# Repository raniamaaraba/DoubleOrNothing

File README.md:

# PCB Development in KiCAD
For this semester, we will be creating custom PCBs (printed circuit boards) in a free software called [KiCAD](https://www.kicad.org/download/), primarily for the use of condensing space inside the avionics bay and to move the club further towards the goal of a space shot in which custom PCBs would be critical to the development of avionics. Before we decide on a final design, in order to easily share and access the schematics, we will be using GitHub as a form of version control. Notably, before we get into the actual logistics of GitHub itself, I wanted to create a comprehensive list _(as of 2/5/26)_ of the parts that we will be using

| Coloquial Name  | Name |
| ------------- | ------------- |
| Microcontroller  | ESP32-S3  |
| Battery | LiPO  |
| Barometer | MS561101BA03-50 |
| IMU | LSM6DSO32TR |
| MOSFET| TBD |
| Resistor| Generic for now |
| Capacitor | Also Generic |

There should be a ZIP file included to help for some of the imports, if you cannot find a specific item you are looking for, please reach out to Loring. Also note the current PCBs on the main branch of KiCAD are primarily for demonstration and by no means are the current version of what we are making. 

# Forking and GitHub
Since I am the owner of this repository, I cannot demonstrate how to fork a repository but I can link you to the GitHub Page about this--click [here](https://docs.github.com/en/pull-requests/collaborating-with-pull-requests/working-with-forks/fork-a-repo) to read how before adding your own commits. This ensure that everyone can keep version control of their PCB without effecting the current main PCB. If you have any issues with Forking this repository (make sure it is the KiCAD branch), please reach out! Also want to note unlike when it come to coding development, it is significantly easier to manage uploading files and pushes using the online GitHub website rather than the desktop.

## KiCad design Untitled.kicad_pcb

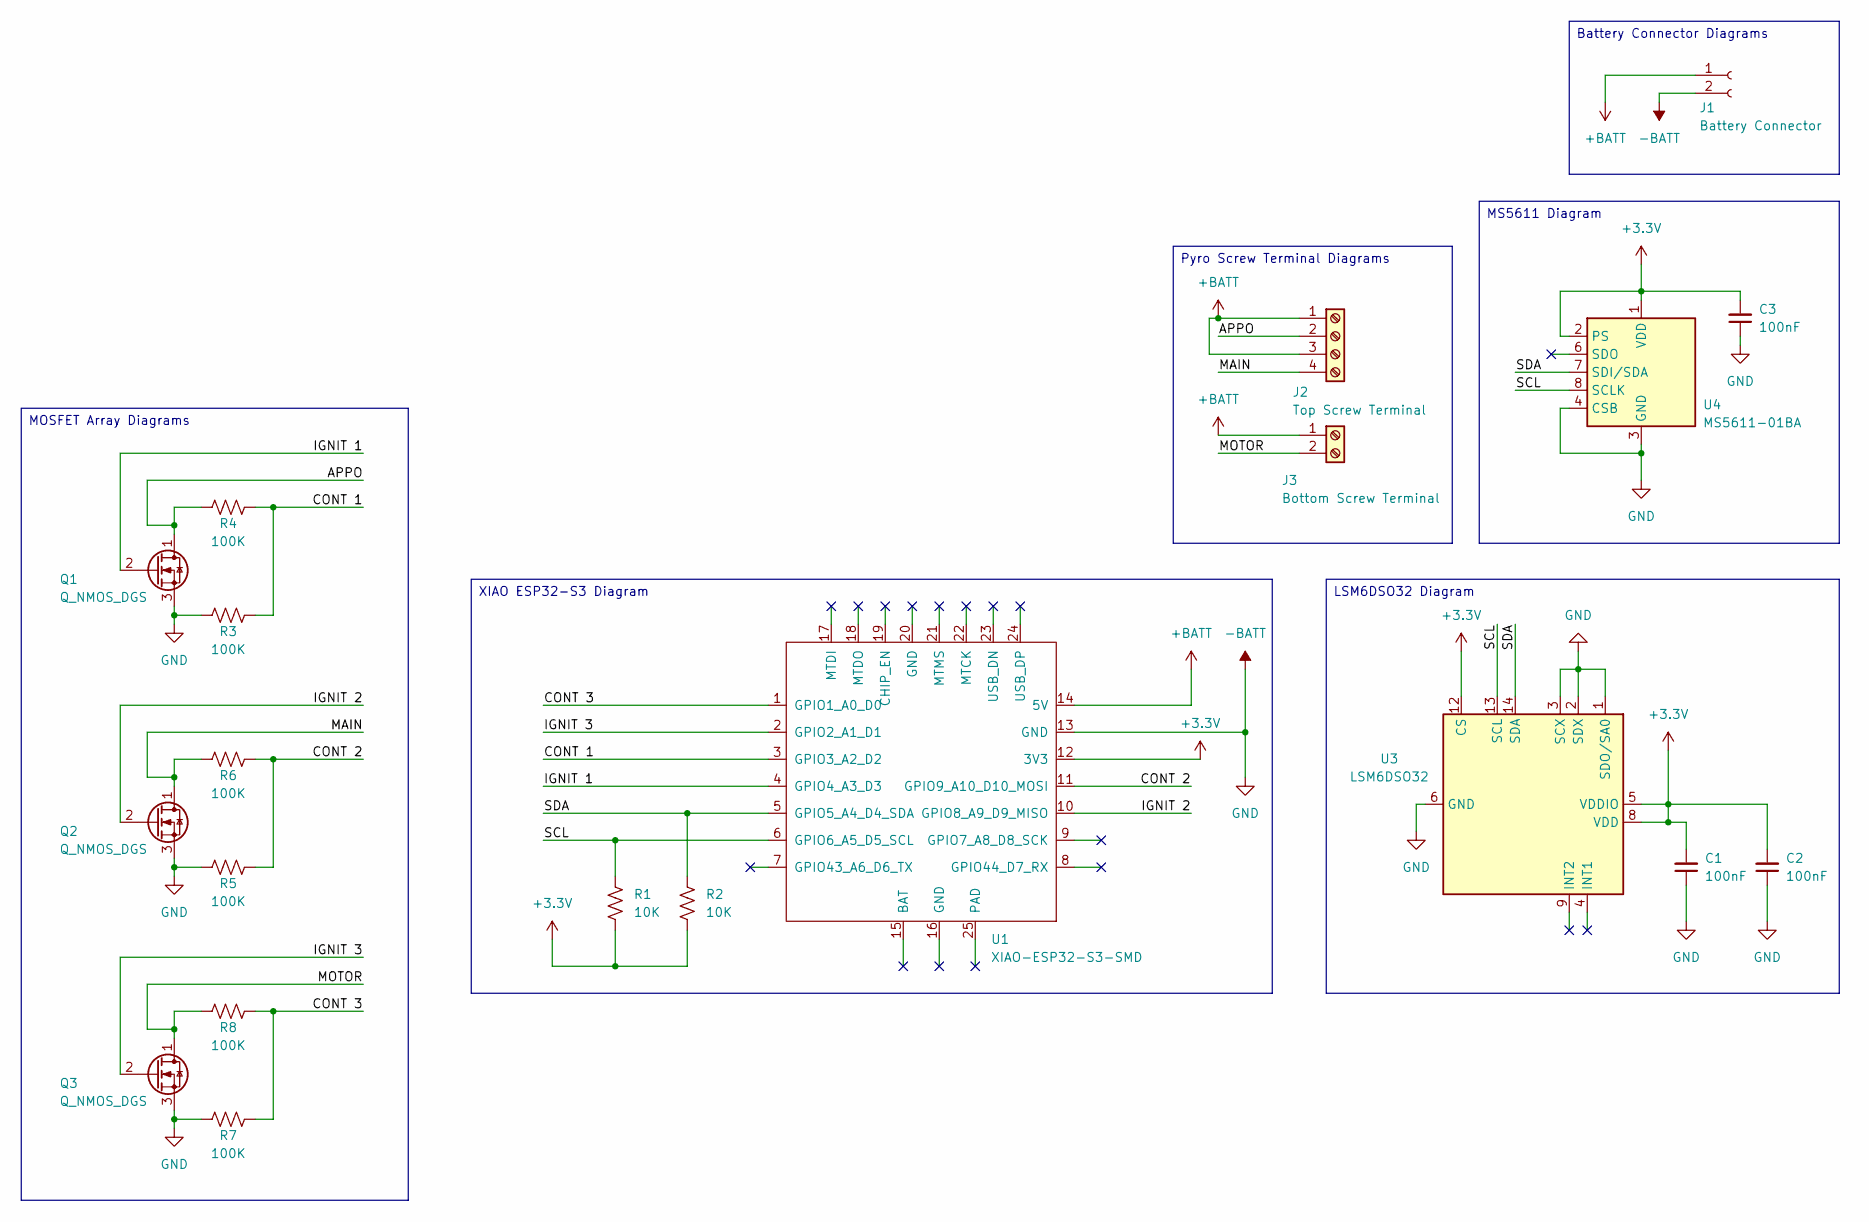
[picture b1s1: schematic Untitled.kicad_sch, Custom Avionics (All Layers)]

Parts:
C1, C2, C3: 100nF; C_0603_1608Metric
J1: Battery Connector; JST_PH_B2B-PH-K_1x02_P2.00mm_Vertical
J2: Top Screw Terminal; TerminalBlock_Phoenix_MPT-0,5-4-2.54_1x04_P2.54mm_Horizontal
J3: Bottom Screw Terminal; TerminalBlock_Phoenix_MPT-0,5-2-2.54_1x02_P2.54mm_Horizontal
Q1, Q2, Q3: Q_NMOS_DGS; TSOT-23
R1, R2: 10K; R_0402_1005Metric
R3, R4, R5, R6, R7, R8: 100K; R_0402_1005Metric
U1: XIAO-ESP32-S3-SMD; XIAO-ESP32S3-DIP
U3: LSM6DSO32; LGA-14_3x2.5mm_P0.5mm_LayoutBorder3x4y
U4: MS5611-01BA; LGA-8_3x5mm_P1.25mm

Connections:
+3.3V: C1.2, C2.2, C3.2, R1.2, R2.2, U1.12 (3V3), U3.5 (VDDIO), U3.8 (VDD), U3.12 (CS), U4.1 (VDD), U4.2 (PS)
+BATT: J1.1, J2.1, J2.3, J3.1, U1.14 (5V)
-BATT: C1.1, C2.1, C3.1, J1.2, Q1.3 (S), Q2.3 (S), Q3.3 (S), R3.2, R5.2, R7.2, U1.13 (GND), U3.1 (SDO/SA0), U3.2 (SDX), U3.3 (SCX), U3.6 (GND), U3.7 (GND), U4.3 (GND), U4.4 (CSB), U4.5 (CSB); also elsewhere on the board
/APPO: J2.2, Q1.1 (D), R4.2
/CONT 1: R3.1, R4.1, U1.3 (GPIO3_A2_D2)
/CONT 2: R5.1, R6.1, U1.11 (GPIO9_A10_D10_MOSI)
/CONT 3: R7.1, R8.1, U1.1 (GPIO1_A0_D0)
/IGNIT 1: Q1.2 (G), U1.4 (GPIO4_A3_D3); also elsewhere on the board
/IGNIT 2: Q2.2 (G), U1.10 (GPIO8_A9_D9_MISO); also elsewhere on the board
/IGNIT 3: Q3.2 (G), U1.2 (GPIO2_A1_D1); also elsewhere on the board
/MAIN: J2.4, Q2.1 (D), R6.2
/MOTOR: J3.2, Q3.1 (D), R8.2
/SCL: R1.1, U1.6 (GPIO6_A5_D5_SCL), U3.13 (SCL), U4.8 (SCLK)
/SDA: R2.1, U1.5 (GPIO5_A4_D4_SDA), U3.14 (SDA), U4.7 (SDI/SDA)

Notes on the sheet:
XIAO ESP32-S3 Diagram
LSM6DSO32 Diagram
MS5611 Diagram
Battery Connector Diagrams
MOSFET Array Diagrams
Pyro Screw Terminal Diagrams

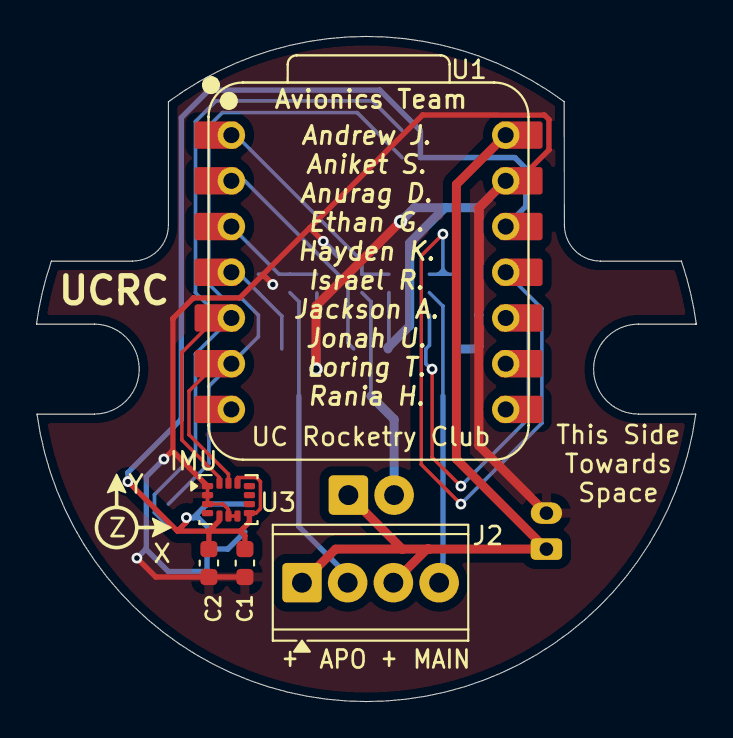
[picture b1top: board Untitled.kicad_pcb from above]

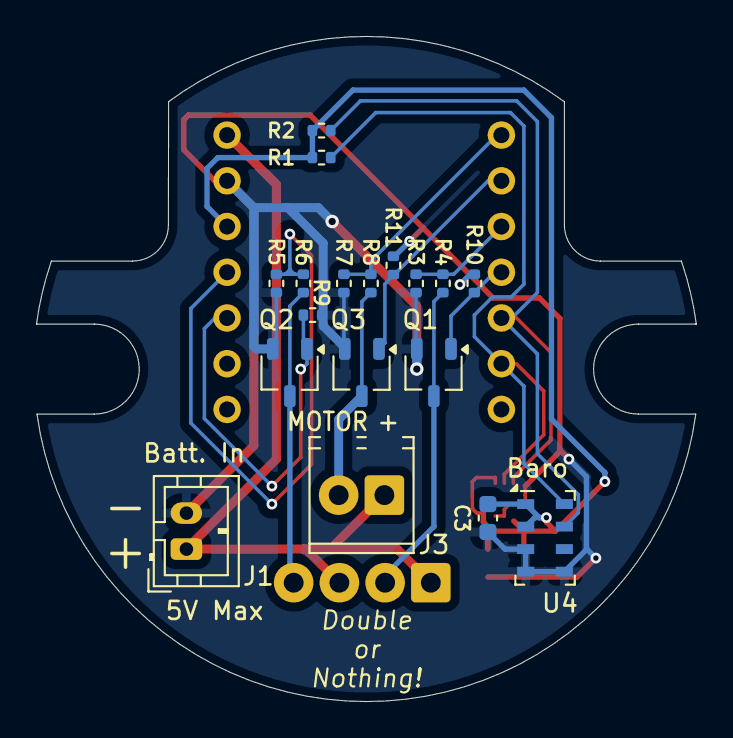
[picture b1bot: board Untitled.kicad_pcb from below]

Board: 2 copper layers, 36.7 x 37.0 mm, 23 parts (18 on the bottom side), 14 nets.

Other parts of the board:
R9, R10, R11: 4.7; R_0402_1005Metric

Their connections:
-BATT: R9.2, R10.2, R11.2; also elsewhere on the board
/IGNIT 1: R10.1; also elsewhere on the board
/IGNIT 2: R9.1; also elsewhere on the board
/IGNIT 3: R11.1; also elsewhere on the board

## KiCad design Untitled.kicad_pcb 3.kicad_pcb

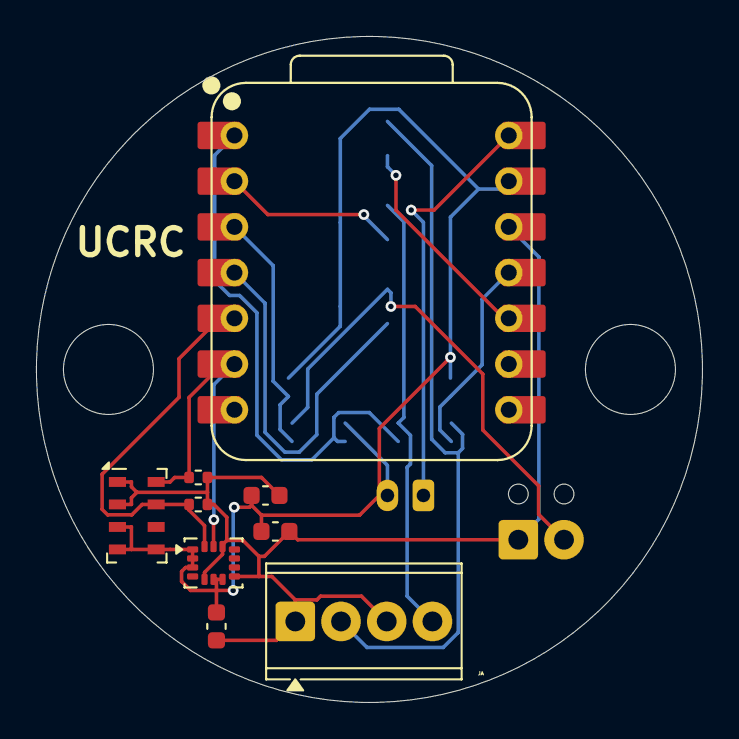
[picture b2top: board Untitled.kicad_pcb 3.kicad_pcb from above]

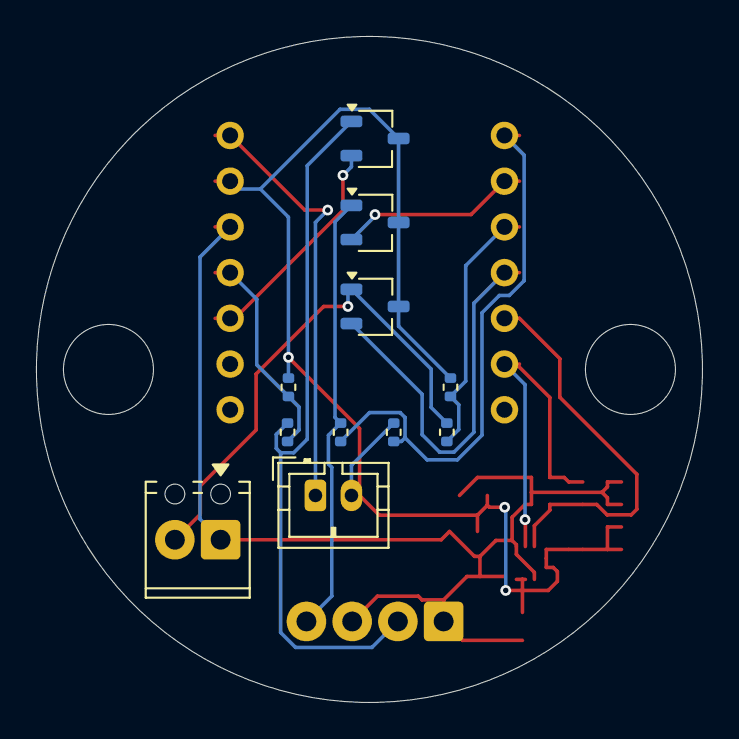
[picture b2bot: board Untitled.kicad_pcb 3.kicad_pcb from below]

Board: 2 copper layers, 37.0 x 37.0 mm, 21 parts (11 on the bottom side), 14 nets.

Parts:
C1, C2, C3: 100nF; C_0603_1608Metric
J1: Battery Connector; JST_PH_B2B-PH-K_1x02_P2.00mm_Vertical
J2: Top Screw Terminal; TerminalBlock_Phoenix_MPT-0,5-4-2.54_1x04_P2.54mm_Horizontal
J3: Bottom Screw Terminal; TerminalBlock_Phoenix_MPT-0,5-2-2.54_1x02_P2.54mm_Horizontal
Q1, Q2, Q3: Q_NMOS_DGS; TSOT-23
R1, R2, R3, R4, R5, R6, R7, R8: 10K; R_0402_1005Metric
Trust: MountingHole_5mm
U1: XIAO-ESP32-S3-SMD; XIAO-ESP32S3-DIP
U3: LSM6DSO32; LGA-14_3x2.5mm_P0.5mm_LayoutBorder3x4y
U4: MS5611-01BA; LGA-8_3x5mm_P1.25mm

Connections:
+3.3V: C1.2, C2.2, C3.2, J2.1, J2.3, J3.1, R1.2, R2.2, U1.12 (3V3), U3.5 (VDDIO), U3.8 (VDD), U3.12 (CS), U4.1 (VDD), U4.2 (PS)
+BATT: J1.1, U1.14 (5V)
-BATT: C1.1, C2.1, C3.1, J1.2, Q1.3 (S), Q2.3 (S), Q3.3 (S), R3.2, R6.2, R8.2, U1.13 (GND), U3.1 (SDO/SA0), U3.2 (SDX), U3.3 (SCX), U3.6 (GND), U3.7 (GND), U4.3 (GND), U4.4 (CSB), U4.5 (CSB)
/APPO: J2.2, Q1.1 (D), R4.2
/CONT 1: R3.1, R4.1, U1.11 (GPIO9_A10_D10_MOSI)
/CONT 2: R5.1, R6.1, U1.1 (GPIO1_A0_D0)
/CONT 3: R7.1, R8.1, U1.3 (GPIO3_A2_D2)
/IGNIT 1: Q1.2 (G), U1.10 (GPIO8_A9_D9_MISO)
/IGNIT 2: Q2.2 (G), U1.2 (GPIO2_A1_D1)
/IGNIT 3: Q3.2 (G), U1.4 (GPIO4_A3_D3)
/MAIN: J2.4, Q2.1 (D), R5.2
/MOTOR: J3.2, Q3.1 (D), R7.2
/SCL: R1.1, U1.6 (GPIO6_A5_D5_SCL), U3.13 (SCL), U4.8 (SCLK)
/SDA: R2.1, U1.5 (GPIO5_A4_D4_SDA), U3.14 (SDA), U4.7 (SDI/SDA)

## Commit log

2026-02-05 Delete
2026-02-05 Updated README
    updated readme for initial setup
2026-02-05 Revise README for PCB development in KiCAD
    Updated project title and added detailed PCB development information, including parts list and forking instructions.
2026-02-05 another url fix
2026-02-06 step files for 3d modeling
2026-02-06 updated code
2026-02-08 Added Correct Microcontroller
    Add the correct symbol for the microcontroller library
2026-02-08 Small Change
2026-02-08 Fixed Microcontroller Library
2026-02-08 Fixed Version Conflicts
    Fixed version issues, should now have all required files in correct versions for the KiCad to run
2026-02-10 Sensor Wiring Finished
    Finished the wiring for both sensors. Cleaned up diagram by using net labels rather than directly connecting everything. Left MOSTFETs unfinished bc they will likely be on a separate board.
2026-02-10 Finished Schematic & Assigned Footprints
    Finished up the schematic, making this version applicable to the entire system rather than a single layer. Assigned footprints for every schematic component, did some very basic layout in the schemat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
2026-02-11 Experimental Layout
    Changed screw terminal footprint to accurately reflect existing club stock of smaller terminals (2.54mm pitch thru-hole). Experimented with trying to make a single board layout work for the flight co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
2026-02-12 Basic Schematic (NO PCB DESIGN DONE)
    Removed any PCB design so people can fork off and do their own PCB designs.
2026-02-16 My PCB design
    I arranged the parts and then used an automatic routing thingy to attach all of the nodes. I then made sure it followed the design rules checker and that's it.
2026-02-16 Added note for sensor reads
    Added a note that shows where to look if people want to see how sensor read functions work
2026-02-17 I forgot to save the PCB file so it autosaved and that's alot of bloat
    Also the design I did is the untitled one, the numbered untitled ones are when i was doing something weird with saving copies but doing that doesn't link it to the schematic file.
2026-02-17 cdr ready pcb design
2026-02-17 Initial Layout
    Did some work on the initial versions of my PCB layout
2026-02-17 Added silkscreens
    Added the silkscreens that have the part numbers onto the PCB Schematic. From what I understand, the silkscreens can go overtop the copper tracks because they are on different layers. If that's not t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
2026-02-20 intial readme for design process
    Added project details, goals, and initial designs for the TwoStageAvionicsBay project. Included information on avionics components and PCB design.
2026-02-26 Changed Mosfet pad arrangement and Screwport terminal location
    Minor silksreen changes were also made.
2026-03-01 Added cutouts, spaced rod holes
    Added cutouts to the side of the PCB for wires to pass through on both sides of the ESP32. Changed distance between screw holes to accurately reflect the spacing used for threaded rods on previous av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
2026-03-01 Initial Routing
    Completed initial manual routing of PCB traces. All nets are fully connected.
2026-03-01 Silkscreen and Cleanup
    Added needed silkscreen elements like screw terminal labels and IMU axis indicator. Also added some UCRC related text and added (placeholder for now) avionics team member names below ESP32 cutout.
2026-03-01 Small Silkscreen Changes
    Added indicator for intended direction and made part label formatting consistent. Also added Jebediah Kerman to the list of fake names
2026-03-04 HTML modifications
2026-03-04 Test
    Test
2026-03-04 Small Changes
    Did some small changes to silkscreen formatting.
2026-03-05 Hole Updates and Initial Names
    Updated the threaded rod holes to extend to the PCB edge due to them previously leaving such a small gap near the sides of the holes. Drill footprints still there for now, will be removed in final ve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
2026-03-05 New Rgs Resistors and Ground Pour
    Added a set of 3 new resistors that bridge the gate of the MOSFETs to ground with a 4.7 ohm resistor, which can help filter out any unintentional activation of the MOSFET due to interference (detaile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
2026-03-05 Tiny Silkscreen Change
    Re-formatted the names silkscreen so that the names look more centered.
2026-03-05 Updated Names and Changed Formatting
    Added a 10th name to the list from the Microsoft Form. Adjusted spacing of several parts of the silkscreen under the ESP32: Separated the "Avionics Team" title from the names, made the names slightly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
2026-03-06 Small Changes
    Moved some trace routing to further prevent potential spacing conflicts.
2026-03-07 Initial Order Version
    Made small adjustments to via layout. Removed drill footprints for threaded rod holes from drawing.
2026-03-11 apogee detection
2026-03-12 math based apogee detection logic
2026-03-13 Moved file management system
    cleaned up main as well as created separate files for file management to declutter
2026-03-13 Simplify Main Code
    Removed all code from main.cpp not related to simple sensor reads and testing. Added some notes to the test_functions.cpp file about how to employ the data_print_test function.
